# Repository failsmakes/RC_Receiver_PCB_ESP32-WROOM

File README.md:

# MakerZ RC Receiver PCB for ESP32-WROOM

Bu proje, [RC-Receiver-ESP](https://github.com/failsmakes/RC-Receiver-ESP) yazılımı için tasarlanmış **ESP32-WROOM tabanlı RC alıcı devresinin PCB çizimini** içerir. Tasarım **KiCad 10.0.1** ile hazırlanmıştır.

## 📌 Proje Özeti
Bu kart, RC sinyallerini ESP32 üzerinden işleyebilmek için optimize edilmiştir. Üzerinde güç regülasyonu, servo ve motor çıkışları, MPU6050 sensör bağlantısı ve MP1584 voltaj modülü için yerleşim alanları bulunur.

## 🧩 Teknik Bileşenler
- **ESP32-WROOM-32 DevKit V1**  
- **MP1584 DC-DC Regülatör Modülü**  
- **MPU6050 IMU Sensör Modülü**  
- **Servo ve Motor çıkış pinleri**  
- **Güç girişleri:** +BATT, +5V, GND  
- **Bağlantı pinleri:** SDA, SCL, INT, VCC  

## 📂 Dosya İçeriği
- `RC_Receiver_PCB_ESP32-WROOM.kicad_pcb` → PCB çizimi  
- `RC_Receiver_PCB_ESP32-WROOM.sch` → Şematik dosyası  
- `MakerZ RC Receiver ESP32 WROOM Schematic.pdf` → Şema PDF çıktısı  
- `gerber/` → Üretim dosyaları  
- `README.md` → Bu açıklama dosyası  

## 🖼️ PCB Görselleri
### Üst Katman

### Alt Katman

## 🚀 Kullanım
1. KiCad ile açarak şematik ve PCB tasarımını inceleyin.  
2. `gerber/` klasöründeki dosyaları kullanarak PCB üretimi yaptırabilirsiniz.  
3. ESP32-WROOM modülünü ve gerekli komponentleri lehimleyerek RC-Receiver-ESP yazılımını yükleyin.  

## 🔗 İlgili Proje
Bu PCB tasarımı, [RC-Receiver-ESP](https://github.com/failsmakes/RC-Receiver-ESP) yazılım projesi ile birlikte kullanılmak üzere hazırlanmıştır.

## 📜 Lisans
Bu proje açık kaynaklıdır. Detaylar için lisans dosyasına göz atın.

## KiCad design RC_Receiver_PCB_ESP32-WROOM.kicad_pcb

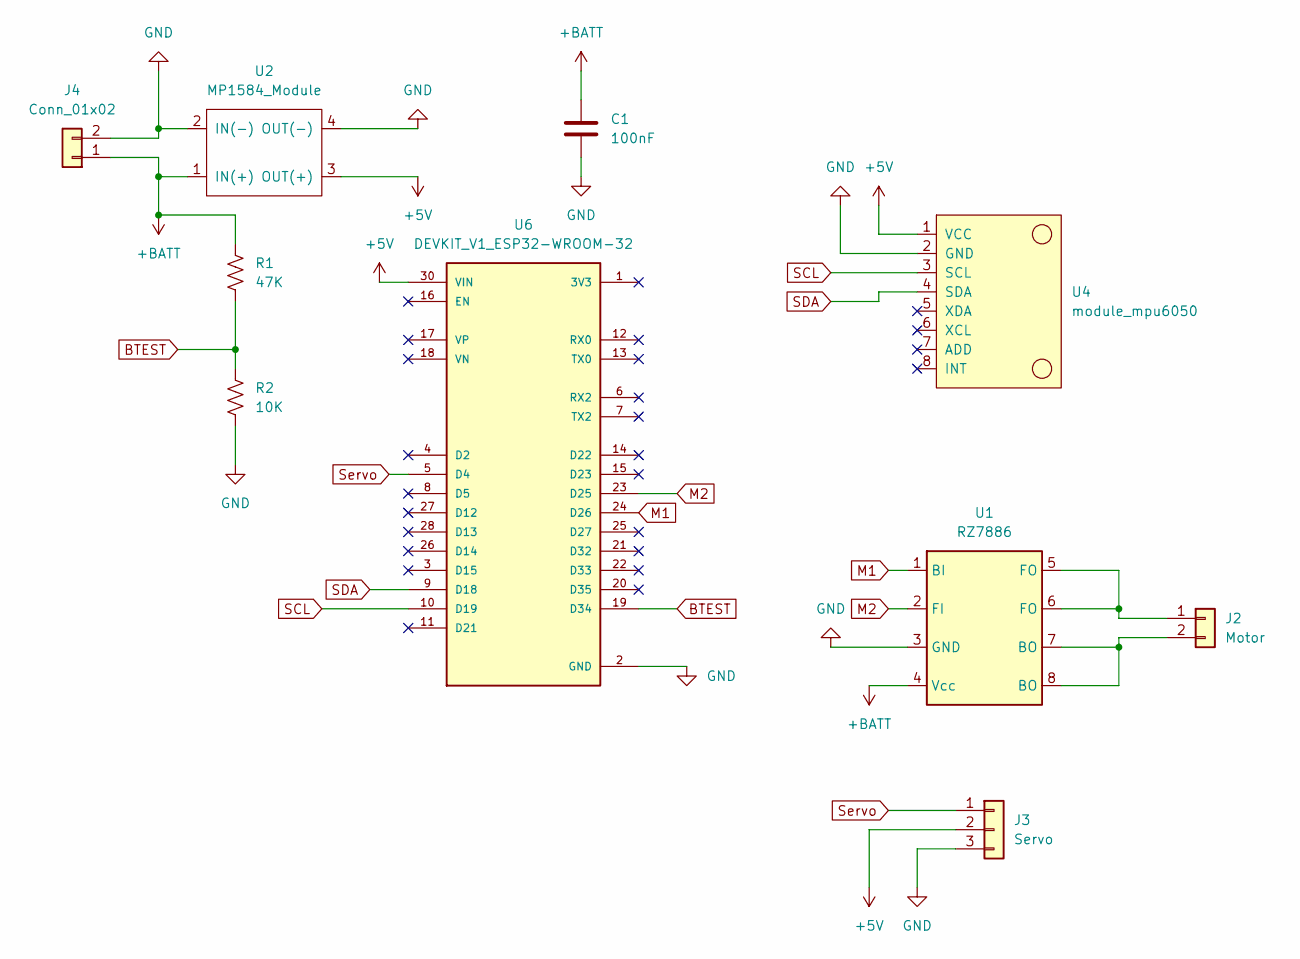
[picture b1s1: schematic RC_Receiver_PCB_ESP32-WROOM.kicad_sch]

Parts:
C1: 100nF; C_Disc_D5.0mm_W2.5mm_P5.00mm
J2: Motor; PinHeader_1x02_P2.54mm_Vertical
J3: Servo; PinHeader_1x03_P2.54mm_Vertical
J4: Conn_01x02; PinHeader_1x02_P2.54mm_Vertical
R1: 47K; R_Axial_DIN0204_L3.6mm_D1.6mm_P7.62mm_Horizontal
R2: 10K; R_Axial_DIN0204_L3.6mm_D1.6mm_P7.62mm_Horizontal
U1: RZ7886; DIP-8_W7.62mm_LongPads
U2: MP1584_Module; SRT_MPT1584EN_Module
U4: module_mpu6050
U6: DEVKIT_V1_ESP32-WROOM-32; MODULE_DEVKIT_V1_ESP32-WROOM-32

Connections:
+5V: J3.2, U2.3 (OUT(+)), U4.1 (VCC), U6.30 (VIN)
+BATT: C1.1, J4.1, R1.1, U1.4 (Vcc), U2.1 (IN(+))
BTEST: R1.2, R2.1, U6.19 (D34)
GND: C1.2, J3.3, J4.2, R2.2, U1.3 (GND), U2.2 (IN(-)), U2.4 (OUT(-)), U4.2 (GND), U6.2 (GND), U6.29 (GND)
M1: U1.1 (BI), U6.24 (D26)
M2: U1.2 (FI), U6.23 (D25)
unnamed: J2.1, U1.5 (FO), U1.6 (FO)
unnamed: J2.2, U1.7 (BO), U1.8 (BO)
SCL: U4.3 (SCL), U6.10 (D19)
SDA: U4.4 (SDA), U6.9 (D18)
Servo: J3.1, U6.5 (D4)

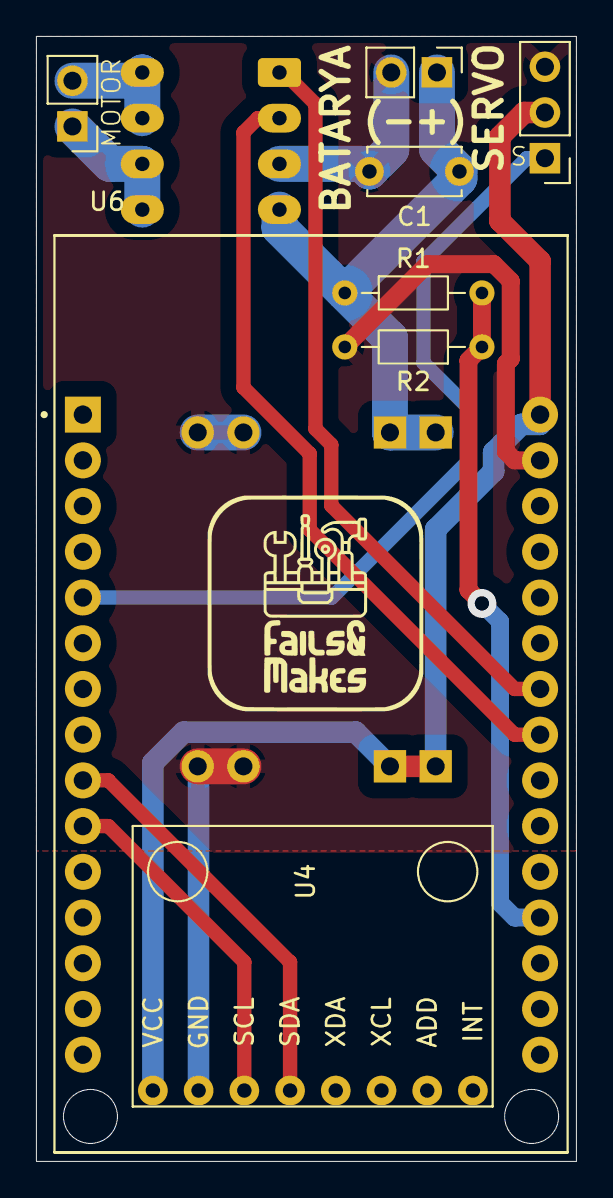
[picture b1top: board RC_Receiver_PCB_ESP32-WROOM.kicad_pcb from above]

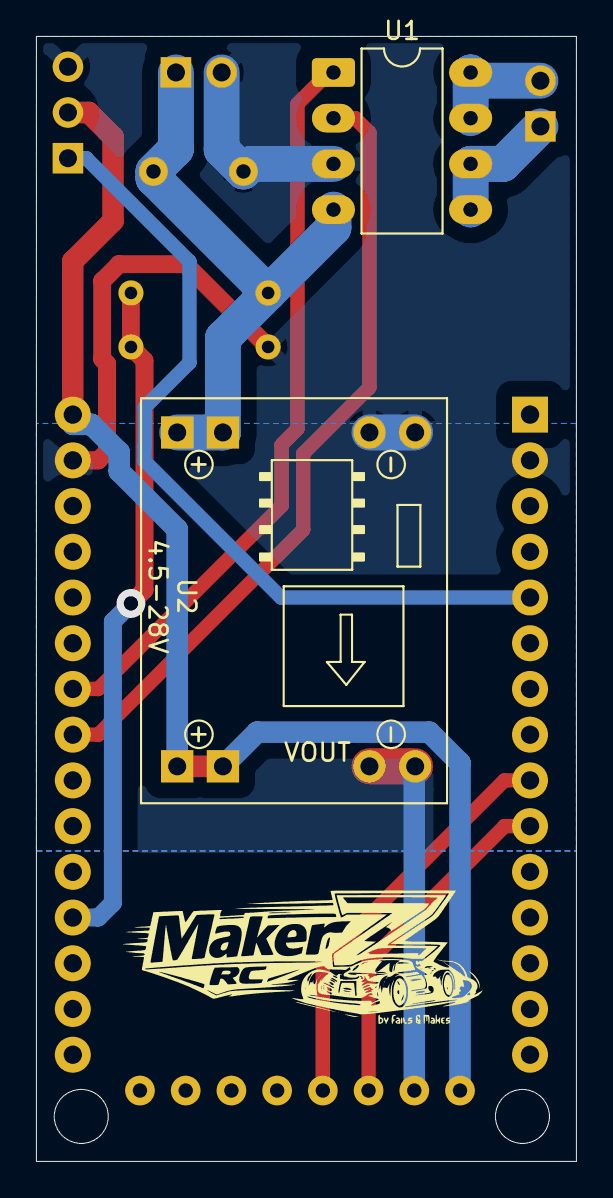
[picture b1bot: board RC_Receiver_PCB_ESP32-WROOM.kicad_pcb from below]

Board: 2 copper layers, 30.0 x 62.5 mm, 10 parts (2 on the bottom side), 11 nets.

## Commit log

2026-05-29 Revise README for RC Receiver PCB project
    Updated README to include project details and usage instructions.
2026-05-29 Pictures
2026-05-29 image update
2026-05-29 Replace PCB images with updated versions
    Updated PCB images in README with new filenames.
